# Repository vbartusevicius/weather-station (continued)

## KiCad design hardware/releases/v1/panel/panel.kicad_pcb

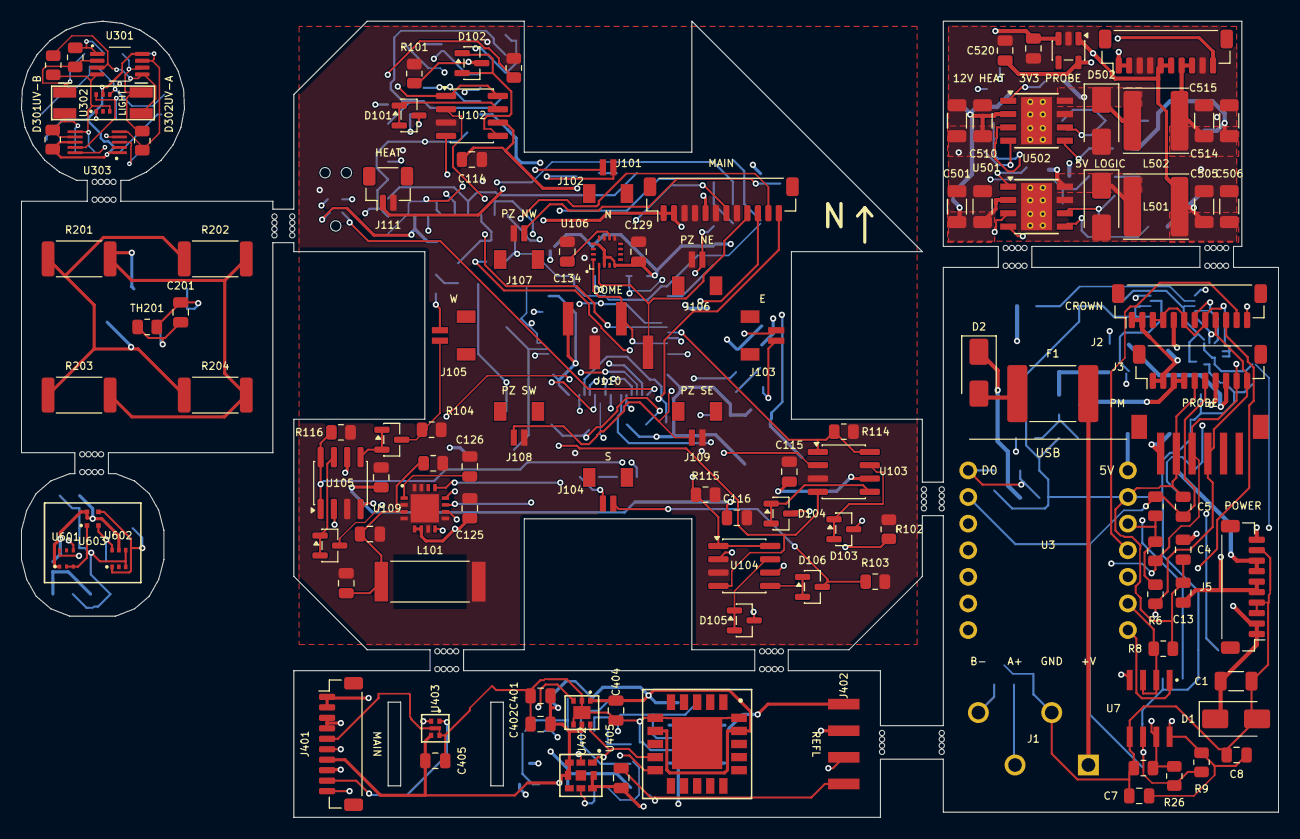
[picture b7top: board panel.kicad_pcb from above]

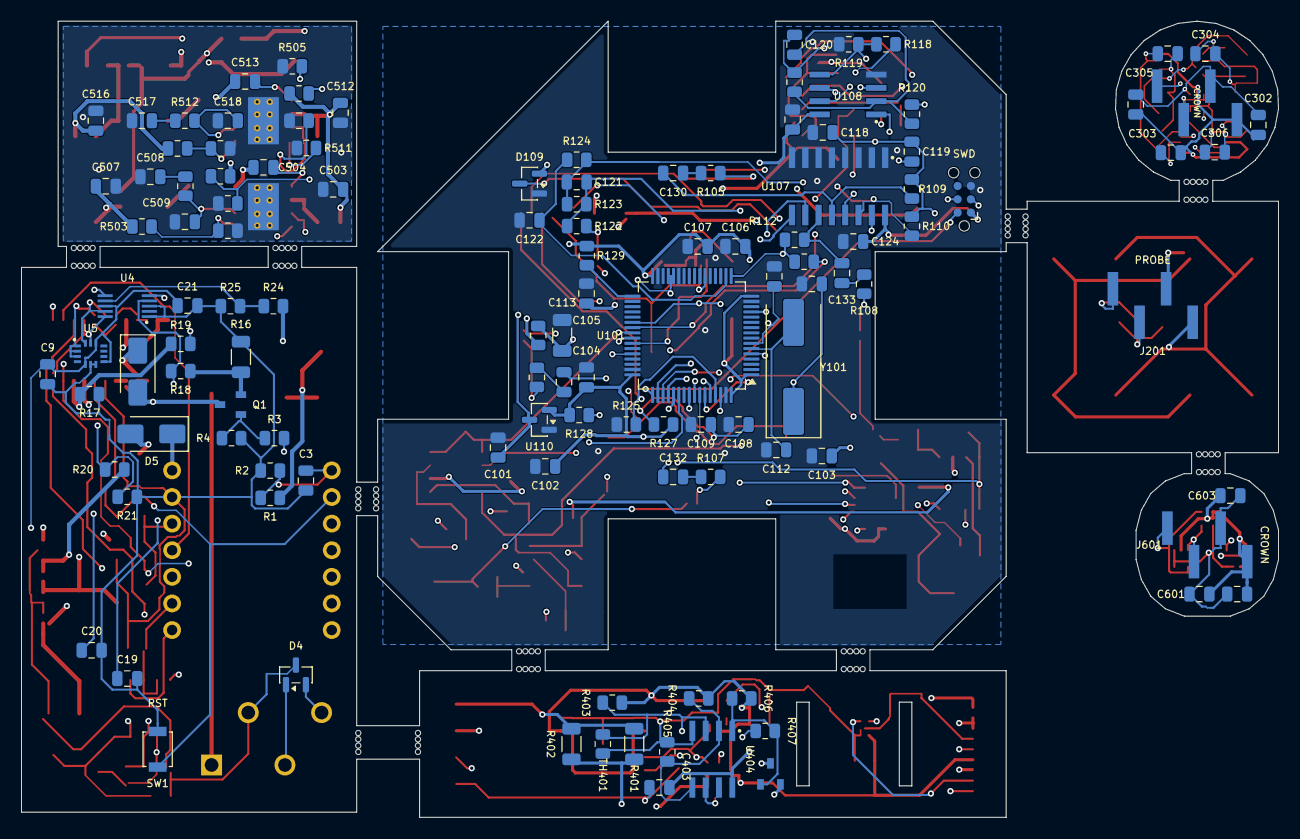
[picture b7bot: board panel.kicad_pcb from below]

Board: 4 copper layers, 120.0 x 76.0 mm, 236 parts (120 on the bottom side), 144 nets.

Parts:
C1, C501, C502, C510, C511: 2u2 100V; C_1206_3216Metric
C3, C5, C7, C8, C9, C21, C103, C104, C105, C106, C109, C110, C119, C123, C124, C129, C201, C301, C302, C303, C402, C403, C404, C405, C406, C504, C507, C513, C516, C601, C602: 100n 50V; C_0805_2012Metric
C4, C13, C102, C107, C134, C401, C520: 10u 10V; C_0805_2012Metric
C19, C20, C101, C108, C114, C115, C116, C117, C118, C125, C126, C306, C519, C603: 1u 50V; C_0805_2012Metric
C111, C112: 33p C0G 50V; C_0805_2012Metric
C113, C514, C515: 22u 25V; C_1206_3216Metric
C120: 220p C0G 50V; C_0805_2012Metric
C121, C305: 22n 50V; C_0805_2012Metric
C122: 1n 50V; C_0805_2012Metric
C127, C128: 470p C0G 50V; C_0805_2012Metric
C130, C131, C132, C133, C304: 10n 50V; C_0805_2012Metric
C503, C512: 100n 100V; C_0805_2012Metric
C505, C506: 47u 10V; C_1206_3216Metric
C508: 33n 50V; C_0805_2012Metric
C509, C518: 68p C0G 50V; C_0805_2012Metric
C517: 18n 50V; C_0805_2012Metric
D1: SMAJ36A; D_SMA
D2, D3: SS16; D_SMA
D4: PSM712; SOT-23
D5: SS14; D_SMA
D101, D102, D103, D104, D105, D106, D107, D108, D109: BAV99; SOT-23
D301: GUVB-C21SD; Genicom_COB2418
D302: GUVA-C22SD; Genicom_COB2418
D501, D502: B360A; D_SMA
F1: 1.1A; Fuse_2920_7451Metric
J1: 12-32V + RS485; TerminalBlock_Kefa_KF250-3.5-4P
J2: Crown board; JST_SH_BM12B-SRSS-TB_1x12-1MP_P1.00mm_Vertical
J3: Probe board; JST_SH_BM10B-SRSS-TB_1x10-1MP_P1.00mm_Vertical
J4: PMSA003I PM; JST_B6B-ZR-SM4-TF
J5: Power board; JST_SH_BM10B-SRSS-TB_1x10-1MP_P1.00mm_Vertical
J101: Main board; JST_SH_BM12B-SRSS-TB_1x12-1MP_P1.00mm_Vertical
J102: XD_N; JST_BM02B-SRSS-TB
J103: XD_E; JST_BM02B-SRSS-TB
J104: XD_S; JST_BM02B-SRSS-TB
J105: XD_W; JST_BM02B-SRSS-TB
J106: PIEZO_NE; JST_BM02B-SRSS-TB
J107: PIEZO_NW; JST_BM02B-SRSS-TB
J108: PIEZO_SW; JST_BM02B-SRSS-TB
J109: PIEZO_SE; JST_BM02B-SRSS-TB
J110: DOME_SOCKET; HX_PZ2.54-1x4P-SMD
J111: AUX 12V_HEAT; JST_SH_BM02B-SRSS-TB_1x02-1MP_P1.00mm_Vertical
J112: SWD; Tag-Connect_TC2030-IDC-NL_2x03_P1.27mm_Vertical
J201: Probe T-Header SMD; HX_PZ2.54-1x4P-SMD
J301, J601: CROWN_RISER; HX_PZ2.54-1x4P-SMD
J401, J501: Main board; JST_SH_BM10B-SRSS-TB_1x10-1MP_P1.00mm_Vertical
J402: Reflector T-Socket SMD; HX_PM2.54-1x4P-RA-SMD
L101: 100uH; AS3935_Antenna_MA5532_SDTR1103
L501: 8.2uH; L_Sunlord_SWPA6045S
L502: 22uH; L_Sunlord_SWPA6045S
MOUSE_BITES: DNP
Q1, Q401: AO3400A; AOS_AO3400A_SOT-23
R1, R4, R303: 100k; R_0805_2012Metric
R2, R7, R8, R21, R24, R25, R118, R119, R125, R126, R128, R129, R304, R403, R404, R406, R510: 10k; R_0805_2012Metric
R3, R101, R102, R103, R104: 330R; R_0805_2012Metric
R5, R6, R113, R114, R115, R116: 2k2; R_0805_2012Metric
R9, R10: 390R; R_0805_2012Metric
R16: 0R1; R_1206_3216Metric
R17: 1R; R_0805_2012Metric
R18, R19, R120, R122: 1k; R_0805_2012Metric
R20: 30k; R_0805_2012Metric
R26: 120R; R_0805_2012Metric
R105, R106, R107, R108, R405: 47k; R_0805_2012Metric
R109, R110, R111, R112: 1M; R_0805_2012Metric
R117, R127: 10R; R_0805_2012Metric
R121: 6k8; R_0805_2012Metric
R123, R302: 4M7; R_0805_2012Metric
R124: 22k; R_0805_2012Metric
R201, R202, R203, R204: 120R; R_2512_6332Metric
R301: 10M; R_0805_2012Metric
R401, R402: 680R; R_1206_3216Metric
R407: 470k; R_0805_2012Metric
R501, R507: 511k; R_0805_2012Metric
R502, R508: 82k5; R_0805_2012Metric
R503: 53k6; R_0805_2012Metric
R504: 10k2; R_0805_2012Metric
R505, R511: 130k; R_0805_2012Metric
R506, R512: 6k49; R_0805_2012Metric
R509: 140k; R_0805_2012Metric
SW1: SERVICE; SW_SPST_B3U-1000P
TH201, TH401: 10k NTC; R_0805_2012Metric
U3: XIAO ESP32C6; XIAO_ESP32C6_Header
U4, U303: ADS1115IDGSR; TI_ADS1115_VSSOP-10
U5: LSM6DS3TR-C; ST_LSM6DS3TR-C_LGA-14
U7: SP3485EN-L/TR; ON_LM393DR2G_SOIC-8
U101: STM32G431RBT6; LQFP-64_10x10mm_P0.5mm
U102, U103, U104, U105: UCC27524ADR; SOIC-8_3.9x4.9mm_P1.27mm
U106: MMC5983MA; MEMSIC_MMC5983MA_LGA-16
U107: 74HC4052D; TI_CD4052BM96_SOIC-16
U108: TLV9062IDR; TI_TLV9062IDR_SOIC-8
U109: AS3935-BQFT; ScioSense_AS3935_QFN-16
U110: XC6206P332MR; SOT-23
U301: TLV9062IDGKR; TI_TLV9062_VSSOP-8
U302, U602: TSL25911FN; AMS_TSL25911FN
U401: SCD41-D-R2; Sensirion_SCD41_LGA-20
U402: SGP41-D-R4; Sensirion_SGP41_DFN-6
U403: SHT40-AD1F-R2; Sensirion_SHT45_DFN-4
U404: LM2903DR2G; ON_LM393DR2G_SOIC-8
U405: BMP585; Bosch_BMP585_LGA-9
U501, U502: TPS54360DDAR; TI_SO-PowerPAD-8_ThermalVias
U503: AP2112K-3.3; SOT-23-5
U601: LTR-390UV-01; LiteOn_LTR-390UV-01
U603: GUVB-C31SM; GenUV_GUVB-C31SM
Y101: 8MHz; Crystal_SMD_HC49-SD

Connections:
+3V3: C7.1, C8.1, C9.1, C21.1, R5.1, R6.1, R7.1, R9.1, U3.12, U4.8, U5.5, U5.8, U5.12, U7.8
+3V3_PROBE: J3.7, J5.10
+5V: C13.1, D5.2, J2.5, J4.1, J5.5, J5.6, R24.1
+5V_XIAO: C4.1, D5.1, U3.14
+12V_HEAT: D3.1, J2.1, J2.2, J3.1, J3.2, J5.7, J5.8, R20.1
CO2_HEAT_RTN: J3.8, R17.1, R19.1
CROWN_+3V3: C102.1, C103.1, C104.1, C105.1, C106.1, C107.1, C123.1, C124.1, C125.1, C129.1, D109.2, J110.1, J112.1, R127.1, R128.2, R129.2, U101.1, U101.16, U101.32, U101.48, U101.64, U106.2, U106.4, U106.13, U107.16, U108.8, U109.5, U109.6, U110.2
CROWN_+3V3A: C108.1, C109.1, R118.1, R127.2, U101.28, U101.29
CROWN_+5V: C101.1, J101.5, U110.3
CROWN_+12V_HEAT: J101.1, J101.2, J111.1, R117.1
CROWN_AS_ACG: C126.1, U109.1
CROWN_AS_CS: U101.51, U109.8
CROWN_AS_INP: C127.1, C128.1, L101.1, R126.1, U109.3
CROWN_AS_IRQ: U101.62, U109.10
CROWN_AS_MISO: U101.57, U109.12
CROWN_AS_MOSI: U101.58, U109.13
CROWN_AS_SCK: U101.56, U109.11
CROWN_BL_PA10: R128.1, U101.44
CROWN_BL_PB12: R129.1, U101.33
CROWN_BOOT0: J2.12, U3.3
CROWN_CROWN_BOOT0: J101.12, R125.1, U101.61
CROWN_CROWN_IRQ: J101.10, U101.54
CROWN_CROWN_NRST: C110.1, J101.11, J112.3, U101.7
CROWN_GND: C101.2, C102.2, C103.2, C104.2, C105.2, C106.2, C107.2, C108.2, C109.2, C110.2, C111.2, C112.2, C113.2, C114.2, C115.2, C116.2, C117.2, C118.2, C122.2, C123.2, C124.2, C125.2, C126.2, C127.2, C128.2, C129.2, C134.2, D109.1, J101.3, J101.4, J101.6, J101.8, J106.2, J107.2, J108.2, J109.2, J110.2, J111.2, J112.5, L101.2, R101.2, R102.2, R103.2, R104.2, R113.2, R114.2, R115.2, R116.2, R119.2, R125.2, R126.2, U101.15, U101.27, U101.31, U101.47, U101.63, U102.3, U103.3, U104.3, U105.3, U106.9, U106.11, U107.1, U107.2, U107.3, U107.4, U107.5, U107.6, U107.7, U107.8, U108.4, U109.2, U109.4, U109.7, U109.9, U109.15, U109.16, U109.17, U110.1
CROWN_I2C_SCL: J101.9, J110.4, U101.22, U106.1
CROWN_I2C_SDA: J101.7, J110.3, U101.42, U106.16
CROWN_IRQ: J2.10, U3.10
CROWN_MAG_CAP: C134.1, U106.10
CROWN_MUX_S0: U101.59, U107.10
CROWN_MUX_S1: U101.60, U107.9
CROWN_NRST: J2.11, U3.11
CROWN_PIEZO_IN: D109.3, J106.1, J107.1, J108.1, J109.1, R122.1
CROWN_PIEZO_INV: C121.1, R122.2, R123.1, U108.6
CROWN_PIEZO_OUT: C121.2, R123.2, R124.1, U108.7
CROWN_RAIN_ADC: C122.1, R124.2, U101.18
CROWN_SWCLK: J112.4, U101.50
CROWN_SWDIO: J112.2, U101.49
CROWN_TX_N: U101.52, U102.4, U103.4, U104.4, U105.4
CROWN_TX_P: U101.38, U102.2, U103.2, U104.2, U105.2
CROWN_US_AMP_FB: C120.1, R120.1, R121.1, U108.2
CROWN_US_AMP_G: C119.1, R120.2
CROWN_US_AMP_OUT: C120.2, R121.2, U101.13, U108.1
CROWN_US_RX_MUX: U107.13, U108.3
CROWN_US_VREF: C118.1, C119.2, R109.2, R110.2, R111.2, R112.2, R118.2, R119.1, U101.17, U108.5
CROWN_VDRV: C113.1, C114.1, C115.1, C116.1, C117.1, R117.2, U102.6, U103.6, U104.6, U105.6
CROWN_XD_EN_E: R114.1, U101.40, U103.1, U103.8
CROWN_XD_EN_N: R113.1, U101.39, U102.1, U102.8
CROWN_XD_EN_S: R115.1, U101.41, U104.1, U104.8
CROWN_XD_EN_W: R116.1, U101.53, U105.1, U105.8
CROWN_XD_E_A: D103.3, J103.1, R106.1
CROWN_XD_E_B: D104.3, J103.2, R102.1
CROWN_XD_E_OUT_A: D103.1, D103.2, U103.7
CROWN_XD_E_OUT_B: D104.1, D104.2, U103.5
CROWN_XD_E_RX: C131.2, R110.1, U107.14
CROWN_XD_E_RXC: C131.1, R106.2
CROWN_XD_N_A: D101.3, J102.1, R105.1
CROWN_XD_N_B: D102.3, J102.2, R101.1
CROWN_XD_N_OUT_A: D101.1, D101.2, U102.7
CROWN_XD_N_OUT_B: D102.1, D102.2, U102.5
CROWN_XD_N_RX: C130.2, R109.1, U107.12
CROWN_XD_N_RXC: C130.1, R105.2
CROWN_XD_S_A: D105.3, J104.1, R107.1
CROWN_XD_S_B: D106.3, J104.2, R103.1
CROWN_XD_S_OUT_A: D105.1, D105.2, U104.7
CROWN_XD_S_OUT_B: D106.1, D106.2, U104.5
CROWN_XD_S_RX: C132.2, R111.1, U107.15
CROWN_XD_S_RXC: C132.1, R107.2
CROWN_XD_W_A: D107.3, J105.1, R108.1
CROWN_XD_W_B: D108.3, J105.2, R104.1
CROWN_XD_W_OUT_A: D107.1, D107.2, U105.7
CROWN_XD_W_OUT_B: D108.1, D108.2, U105.5
CROWN_XD_W_RX: C133.2, R112.1, U107.11
CROWN_XD_W_RXC: C133.1, R108.2
CROWN_XTAL_IN: C111.1, U101.5, Y101.1
CROWN_XTAL_OUT: C112.1, U101.6, Y101.2
DOME_+3V3: C301.1, C302.1, C303.1, J301.1, R303.1, U301.8, U302.5, U303.1, U303.8
DOME_GND: C301.2, C302.2, C303.2, C306.2, J301.2, R304.2, U301.4, U302.3, U302.4, U303.3, U303.6
DOME_I2C_SCL: J301.4, U302.1, U303.10
DOME_I2C_SDA: J301.3, U302.6, U303.9
DOME_LEGACY_+3V3: C601.1, C602.1, C603.1, J601.1, U601.1, U602.5, U603.4
DOME_LEGACY_GND: C601.2, C602.2, C603.2, J601.2, U601.2, U601.3, U602.3, U602.4, U603.1
DOME_LEGACY_I2C_SCL: J601.4, U601.4, U602.1, U603.3
DOME_LEGACY_I2C_SDA: J601.3, U601.6, U602.6, U603.2
DOME_UVA_IN: C305.1, D302.2, R302.1, U301.6
DOME_UVA_OUT: C305.2, R302.2, U301.7, U303.5
DOME_UVB_IN: C304.1, D301.2, R301.1, U301.2
DOME_UVB_OUT: C304.2, R301.2, U301.1, U303.4
DOME_UV_VB: C306.1, D301.1, D302.1, R303.2, R304.1, U301.3, U301.5, U303.7
GND: C1.2, C3.2, C4.2, C5.2, C7.2, C8.2, C9.2, C13.2, C19.2, C20.2, C21.2, D1.2, D4.3, J1.2, J2.3, J2.4, J2.6, J2.8, J3.5, J4.2, J5.3, J5.4, J5.9, R2.2, R4.2, R8.2, R10.2, R16.2, R17.2, R21.2, R25.2, SW1.2, U3.13, U4.1, U4.3, U5.1, U5.2, U5.3, U5.6, U5.7, U7.5
HEAT_GATE: Q1.1, R3.2, R4.1
HEAT_PWM: R3.1, U3.4
HEAT_SENSE: Q1.2, R16.1, R18.1
HEAT_SW: D3.2, J3.3, J3.4, Q1.3
I2C_SCL: J2.9, J3.10, J4.4, R6.2, U3.6, U4.10, U5.13
I2C_SDA: J2.7, J3.9, J4.3, R5.2, U3.5, U4.9, U5.14
MON_5V: R20.2, R21.1, U4.6
MON_5V_LOGIC: R24.2, R25.1, U4.7
MON_PROBE: C20.1, R19.2, U4.5
MON_REFL: C19.1, R18.2, U4.4
NTC_SENSE: C5.1, J3.6, R7.2, SW1.1, U3.2
POWER_+3V3_PROBE: C520.1, J501.10, U503.5
POWER_+5V: C505.1, C506.1, C507.1, C519.1, J501.5, J501.6, L501.2, R503.1, U503.1, U503.3
POWER_+12V_HEAT: C514.1, C515.1, C516.1, J501.7, J501.8, L502.2, R509.1
POWER_GND: C501.2, C502.2, C503.2, C505.2, C506.2, C507.2, C508.2, C509.2, C510.2, C511.2, C512.2, C514.2, C515.2, C516.2, C517.2, C518.2, C519.2, C520.2, D501.2, D502.2, J501.3, J501.4, J501.9, R502.2, R504.2, R505.2, R508.2, R510.2, R511.2, U501.7, U501.9, U502.7, U502.9, U503.2
POWER_HEAT_BST: C513.1, U502.1
POWER_HEAT_CC: C517.1, R512.2
POWER_HEAT_COMP: C518.1, R512.1, U502.6
POWER_HEAT_EN: R507.2, R508.1, U502.3
POWER_HEAT_FB: R509.2, R510.1, U502.5
POWER_HEAT_RT: R511.1, U502.4
POWER_HEAT_SW: C513.2, D502.1, L502.1, U502.8
POWER_LOGIC_BST: C504.1, U501.1
POWER_LOGIC_CC: C508.1, R506.2
POWER_LOGIC_COMP: C509.1, R506.1, U501.6
POWER_LOGIC_EN: R501.2, R502.1, U501.3
POWER_LOGIC_FB: R503.2, R504.1, U501.5
POWER_LOGIC_RT: R505.1, U501.4
POWER_LOGIC_SW: C504.2, D501.1, L501.1, U501.8
POWER_VIN_PROT: C501.1, C502.1, C503.1, C510.1, C511.1, C512.1, J501.1, J501.2, R501.1, R507.1, U501.2, U502.2
PROBE_+3V3_PROBE: C401.1, C402.1, C404.1, C405.1, C406.1, J401.7, R403.1, R404.1, R406.1, U401.7, U401.19, U402.1, U402.5, U403.3, U405.3, U405.4, U405.7, U405.8
PROBE_+12V_HEAT: C403.1, J401.1, J401.2, J402.1, R401.1, R402.1, U404.8
PROBE_CO2_GATE: Q401.1, R406.2, R407.1, U404.1
PROBE_CO2_HEAT_RTN: J401.8, Q401.2
PROBE_CO2_HEAT_SW: Q401.3, R401.2, R402.2
PROBE_CO2_NTC: R403.2, R407.2, TH401.1, U404.3
PROBE_CO2_VSET: R404.2, R405.1, U404.2, U404.5
PROBE_GND: C401.2, C402.2, C403.2, C404.2, C405.2, C406.2, J401.5, J402.4, R405.2, TH401.2, U401.6, U401.20, U401.21, U402.2, U402.4, U402.7, U403.4, U403.5, U404.4, U404.6, U405.6
PROBE_HEAT_SW: J401.3, J401.4, J402.2
PROBE_I2C_SCL: J401.10, U401.9, U402.6, U403.2, U405.1
PROBE_I2C_SDA: J401.9, U401.10, U402.3, U403.1, U405.2
PROBE_NTC_SENSE: J401.6, J402.3
REFLECTOR_+12V_HEAT: J201.1, R201.1, R202.1, R203.1, R204.1
REFLECTOR_GND: C201.2, J201.4, TH201.2
REFLECTOR_HEAT_SW: J201.2, R201.2, R202.2, R203.2, R204.2
REFLECTOR_NTC_SENSE: C201.1, J201.3, TH201.1
RS485_A: D4.1, J1.3, R9.2, R26.1, U7.6
RS485_B: D4.2, J1.4, R10.1, R26.2, U7.7
RS485_DE: R8.1, U3.9, U7.2, U7.3
RS485_RX: U3.8, U7.1
RS485_TX: U3.7, U7.4
VIN_ADC: C3.1, R1.2, R2.1, U3.1
VIN_FUSED: D2.2, F1.2
VIN_PROT: C1.1, D1.1, D2.1, J5.1, J5.2, R1.1
VIN_RAW: F1.1, J1.1

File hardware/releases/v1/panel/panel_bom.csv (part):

Line,Qty,Designators,Value,Package,Type,Manufacturer,MPN,LCSC,Assembly
1,5,"C1,C501,C502,C510,C511",2u2 100V,C_1206_3216Metric,SMD,Samsung,CL31B225KCHSNNE,C170101,machine
2,14,"C101,C108,C114,C115,C116,C117,C118,C125,C126,C19,C20,C306,C519,C603",1u 50V,C_0805_2012Metric,SMD,Samsung,CL21B105KBFNNNE,C28323,machine
3,7,"C102,C107,C13,C134,C4,C401,C520",10u 10V,C_0805_2012Metric,SMD,Samsung,CL21A106KPFNNNE,C17024,machine
4,31,"C103,C104,C105,C106,C109,C110,C119,C123,C124,C129,C201,C21,C3,C301,C302,C303,C402,C403,C404,C405,C406,C5,C504,C507,C513,C516,C601,C602,C7,C8,C9",100n 50V,C_0805_2012Metric,SMD,YAGEO,CC0805KRX7R9BB104,C49678,machine
5,2,"C111,C112",33p C0G 50V,C_0805_2012Metric,SMD,YAGEO,CC0805JRNPO9BN330,C107115,machine
6,3,"C113,C514,C515",22u 25V,C_1206_3216Metric,SMD,Samsung,CL31A226KAHNNNE,C12891,machine
7,1,C120,220p C0G 50V,C_0805_2012Metric,SMD,YAGEO,CC0805JRNPO9BN221,C107112,machine
8,2,"C121,C305",22n 50V,C_0805_2012Metric,SMD,YAGEO,CC0805KRX7R9BB223,C107147,machine
9,1,C122,1n 50V,C_0805_2012Metric,SMD,YAGEO,CC0805KRX7R9BB102,C94121,machine
10,2,"C127,C128",470p C0G 50V,C_0805_2012Metric,SMD,YAGEO,CC0805JRNPO9BN471,C62771,machine
11,5,"C130,C131,C132,C133,C304",10n 50V,C_0805_2012Metric,SMD,YAGEO,CC0805KRX7R9BB103,C83170,machine
12,2,"C503,C512",100n 100V,C_0805_2012Metric,SMD,YAGEO,CC0805KKX7R0BB104,C106243,machine
13,2,"C505,C506",47u 10V,C_1206_3216Metric,SMD,Samsung,CL31A476MPHNNNE,C96123,machine
14,1,C508,33n 50V,C_0805_2012Metric,SMD,YAGEO,CC0805KRX7R9BB333,C107150,machine
15,2,"C509,C518",68p C0G 50V,C_0805_2012Metric,SMD,YAGEO,CC0805JRNPO9BN680,C107120,machine
16,1,C517,18n 50V,C_0805_2012Metric,SMD,YAGEO,CC0805JRX7R9BB183,C520032,machine
17,1,D1,SMAJ36A,D_SMA,SMD,MDD,SMAJ36A,C113967,machine
18,9,"D101,D102,D103,D104,D105,D106,D107,D108,D109",BAV99,SOT-23,SMD,Nexperia,"BAV99,215",C2500,machine
19,2,"D2,D3",SS16,D_SMA,SMD,MDD,SS16,C2481,machine
20,1,D301,GUVB-C21SD,Genicom_COB2418,SMD,Genicom,GUVB-C21SD,,hand-fit (not stocked by JLCPCB)
21,1,D302,GUVA-C22SD,Genicom_COB2418,SMD,Genicom,GUVA-C22SD,,hand-fit (not stocked by JLCPCB)
22,1,D4,PSM712,SOT-23,SMD,Protek,PSM712-LF-T7,C32677,machine
23,1,D5,SS14,D_SMA,SMD,MDD,SS14,C2480,machine
24,2,"D501,D502",B360A,D_SMA,SMD,Diodes Inc,B360A-13-F,C94193,machine
25,1,F1,1.1A,Fuse_2920_7451Metric,SMD,Littelfuse,2920L110/60V,C49318488,machine
26,1,J1,12-32V + RS485,TerminalBlock_Kefa_KF250-3.5-4P,THT,Cixi Kefa Elec,KF250-3.5-4P-1,C475156,machine
27,1,J101,Main board,JST_SH_BM12B-SRSS-TB_1x12-1MP_P1.00mm_Vertical,SMD,JST,BM12B-SRSS-TB(LF)(SN),C160398,machine
28,1,J102,XD_N,JST_BM02B-SRSS-TB,SMD,JST,BM02B-SRSS-TB(LF)(SN),C160388,machine
29,1,J103,XD_E,JST_BM02B-SRSS-TB,SMD,JST,BM02B-SRSS-TB(LF)(SN),C160388,machine
30,1,J104,XD_S,JST_BM02B-SRSS-TB,SMD,JST,BM02B-SRSS-TB(LF)(SN),C160388,machine
31,1,J105,XD_W,JST_BM02B-SRSS-TB,SMD,JST,BM02B-SRSS-TB(LF)(SN),C160388,machine
32,1,J106,PIEZO_NE,JST_BM02B-SRSS-TB,SMD,JST,BM02B-SRSS-TB(LF)(SN),C160388,machine
33,1,J107,PIEZO_NW,JST_BM02B-SRSS-TB,SMD,JST,BM02B-SRSS-TB(LF)(SN),C160388,machine
34,1,J108,PIEZO_SW,JST_BM02B-SRSS-TB,SMD,JST,BM02B-SRSS-TB(LF)(SN),C160388,machine
35,1,J109,PIEZO_SE,JST_BM02B-SRSS-TB,SMD,JST,BM02B-SRSS-TB(LF)(SN),C160388,machine
36,1,J110,DOME_SOCKET,HX_PZ2.54-1x4P-SMD,SMD,HCTL,HX PM2.54-1x4P TP-YQ,C42379197,machine
37,1,J111,AUX 12V_HEAT,JST_SH_BM02B-SRSS-TB_1x02-1MP_P1.00mm_Vertical,SMD,JST,BM02B-SRSS-TB(LF)(SN),C160388,machine
38,1,J2,Crown board,JST_SH_BM12B-SRSS-TB_1x12-1MP_P1.00mm_Vertical,SMD,JST,BM12B-SRSS-TB(LF)(SN),C160398,machine
39,1,J201,Probe T-Header SMD,HX_PZ2.54-1x4P-SMD,SMD,HANBO,HX PZ2.54-1x4P TP-YQ,C41417361,machine
40,1,J3,Probe board,JST_SH_BM10B-SRSS-TB_1x10-1MP_P1.00mm_Vertical,SMD,JST,BM10B-SRSS-TB(LF)(SN),C160396,machine
41,2,"J301,J601",CROWN_RISER,HX_PZ2.54-1x4P-SMD,SMD,HCTL,HX PZ2.54-1x4P TP-YQ,C41417361,machine
42,1,J4,PMSA003I PM,JST_B6B-ZR-SM4-TF,SMD,JST,B6B-ZR-SM4-TF(LF)(SN),C471473,machine
43,2,"J401,J501",Main board,JST_SH_BM10B-SRSS-TB_1x10-1MP_P1.00mm_Vertical,SMD,JST,BM10B-SRSS-TB(LF)(SN),C160396,machine
44,1,J402,Reflector T-Socket SMD,HX_PM2.54-1x4P-RA-SMD,SMD,HANBO,HX PM2.54-1x4P WT,C46061768,machine
45,1,J5,Power board,JST_SH_BM10B-SRSS-TB_1x10-1MP_P1.00mm_Vertical,SMD,JST,BM10B-SRSS-TB(LF)(SN),C160396,machine
46,1,L101,100uH,AS3935_Antenna_MA5532_SDTR1103,SMD,Coilcraft,MA5532-AE,,hand-fit (not stocked by JLCPCB)
47,1,L501,8.2uH,L_Sunlord_SWPA6045S,SMD,APV,ANR6045T8R2M,C7427168,machine
48,1,L502,22uH,L_Sunlord_SWPA6045S,SMD,Bourns,SRN6045TA-220M,C2044314,machine
49,2,"Q1,Q401",AO3400A,AOS_AO3400A_SOT-23,SMD,Alpha & Omega Semicon,AO3400A,C20917,machine
50,3,"R1,R303,R4",100k,R_0805_2012Metric,SMD,UNI-ROYAL,0805W8F1003T5E,C149504,machine
51,2,"R10,R9",390R,R_0805_2012Metric,SMD,UNI-ROYAL,0805W8F3900T5E,C17655,machine
52,5,"R101,R102,R103,R104,R3",330R,R_0805_2012Metric,SMD,UNI-ROYAL,0805W8F3300T5E,C17630,machine
53,5,"R105,R106,R107,R108,R405",47k,R_0805_2012Metric,SMD,UNI-ROYAL,0805W8F4702T5E,C17713,machine
54,4,"R109,R110,R111,R112",1M,R_0805_2012Metric,SMD,UNI-ROYAL,0805W8F1004T5E,C17514,machine
55,6,"R113,R114,R115,R116,R5,R6",2k2,R_0805_2012Metric,SMD,UNI-ROYAL,0805W8F2201T5E,C17520,machine
56,2,"R117,R127",10R,R_0805_2012Metric,SMD,UNI-ROYAL,0805W8F100JT5E,C17415,machine
57,17,"R118,R119,R125,R126,R128,R129,R2,R21,R24,R25,R304,R403,R404,R406,R510,R7,R8",10k,R_0805_2012Metric,SMD,UNI-ROYAL,0805W8F1002T5E,C17414,machine
58,4,"R120,R122,R18,R19",1k,R_0805_2012Metric,SMD,UNI-ROYAL,0805W8F1001T5E,C17513,machine
59,1,R121,6k8,R_0805_2012Metric,SMD,UNI-ROYAL,0805W8F6801T5E,C17772,machine
60,2,"R123,R302",4M7,R_0805_2012Metric,SMD,UNI-ROYAL,0805W8F4704T5E,C17674,machine
61,1,R124,22k,R_0805_2012Metric,SMD,UNI-ROYAL,0805W8F2202T5E,C17560,machine
62,1,R16,0R1,R_1206_3216Metric,SMD,UNI-ROYAL,1206W4F100LT5E,C25334,machine
63,1,R17,1R,R_0805_2012Metric,SMD,UNI-ROYAL,0805W8F100KT5E,C25271,machine
64,1,R20,30k,R_0805_2012Metric,SMD,UNI-ROYAL,0805W8F3002T5E,C17621,machine
65,4,"R201,R202,R203,R204",120R,R_2512_6332Metric,SMD,YAGEO,RC2512FK-7W120RL,C7276687,machine
66,1,R26,120R,R_0805_2012Metric,SMD,UNI-ROYAL,0805W8F1200T5E,C17437,hand-fit (not stocked by JLCPCB)
67,1,R301,10M,R_0805_2012Metric,SMD,UNI-ROYAL,0805W8F1005T5E,C26108,machine
68,2,"R401,R402",680R,R_1206_3216Metric,SMD,FOJAN,FRP1206F6800TS,C48533685,machine
69,1,R407,470k,R_0805_2012Metric,SMD,UNI-ROYAL,0805W8F4703T5E,C17709,machine
70,2,"R501,R507",511k,R_0805_2012Metric,SMD,UNI-ROYAL,0805W8F5113T5E,C17735,machine
71,2,"R502,R508",82k5,R_0805_2012Metric,SMD,YAGEO,RC0805FR-0782K5L,C276314,machine
72,1,R503,53k6,R_0805_2012Metric,SMD,UNI-ROYAL,0805W8F5362T5E,C21398,machine
73,1,R504,10k2,R_0805_2012Metric,SMD,UNI-ROYAL,0805W8F1022T5E,C17402,machine
74,2,"R505,R511",130k,R_0805_2012Metric,SMD,UNI-ROYAL,0805W8F1303T5E,C17450,machine
75,2,"R506,R512",6k49,R_0805_2012Metric,SMD,UNI-ROYAL,0805W8F6491T5E,C17769,machine
76,1,R509,140k,R_0805_2012Metric,SMD,UNI-ROYAL,0805W8F1403T5E,C17460,machine
77,1,SW1,SERVICE,SW_SPST_B3U-1000P,SMD,Omron,B3U-1000P,C231329,machine
78,2,"TH201,TH401",10k NTC,R_0805_2012Metric,SMD,R+O,HNTC0805-103F3950FB,C49247662,machine
79,1,U101,STM32G431RBT6,LQFP-64_10x10mm_P0.5mm,SMD,STMicroelectronics,STM32G431RBT6,C431633,machine
80,4,"U102,U103,U104,U105",UCC27524ADR,SOIC-8_3.9x4.9mm_P1.27mm,SMD,Texas Instruments,UCC27524ADR,C185857,machine
81,1,U106,MMC5983MA,MEMSIC_MMC5983MA_LGA-16,SMD,MEMSIC,MMC5983MA,C404329,machine
82,1,U107,74HC4052D,TI_CD4052BM96_SOIC-16,SMD,Nexperia,"74HC4052D,653",C11350,machine
83,1,U108,TLV9062IDR,TI_TLV9062IDR_SOIC-8,SMD,Texas Instruments,TLV9062IDR,C398355,machine
84,1,U109,AS3935-BQFT,ScioSense_AS3935_QFN-16,SMD,ScioSense,AS3935-BQFT,,hand-fit (not stocked by JLCPCB)
85,1,U110,XC6206P332MR,SOT-23,SMD,Torex,XC6206P332MR-G,C5446,machine
86,1,U3,XIAO ESP32C6,XIAO_ESP32C6_Header,THT,Seeed Studio,102010636,,hand-fit (not stocked by JLCPCB)
87,1,U301,TLV9062IDGKR,TI_TLV9062_VSSOP-8,SMD,Texas Instruments,TLV9062IDGKR,C398356,machine
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
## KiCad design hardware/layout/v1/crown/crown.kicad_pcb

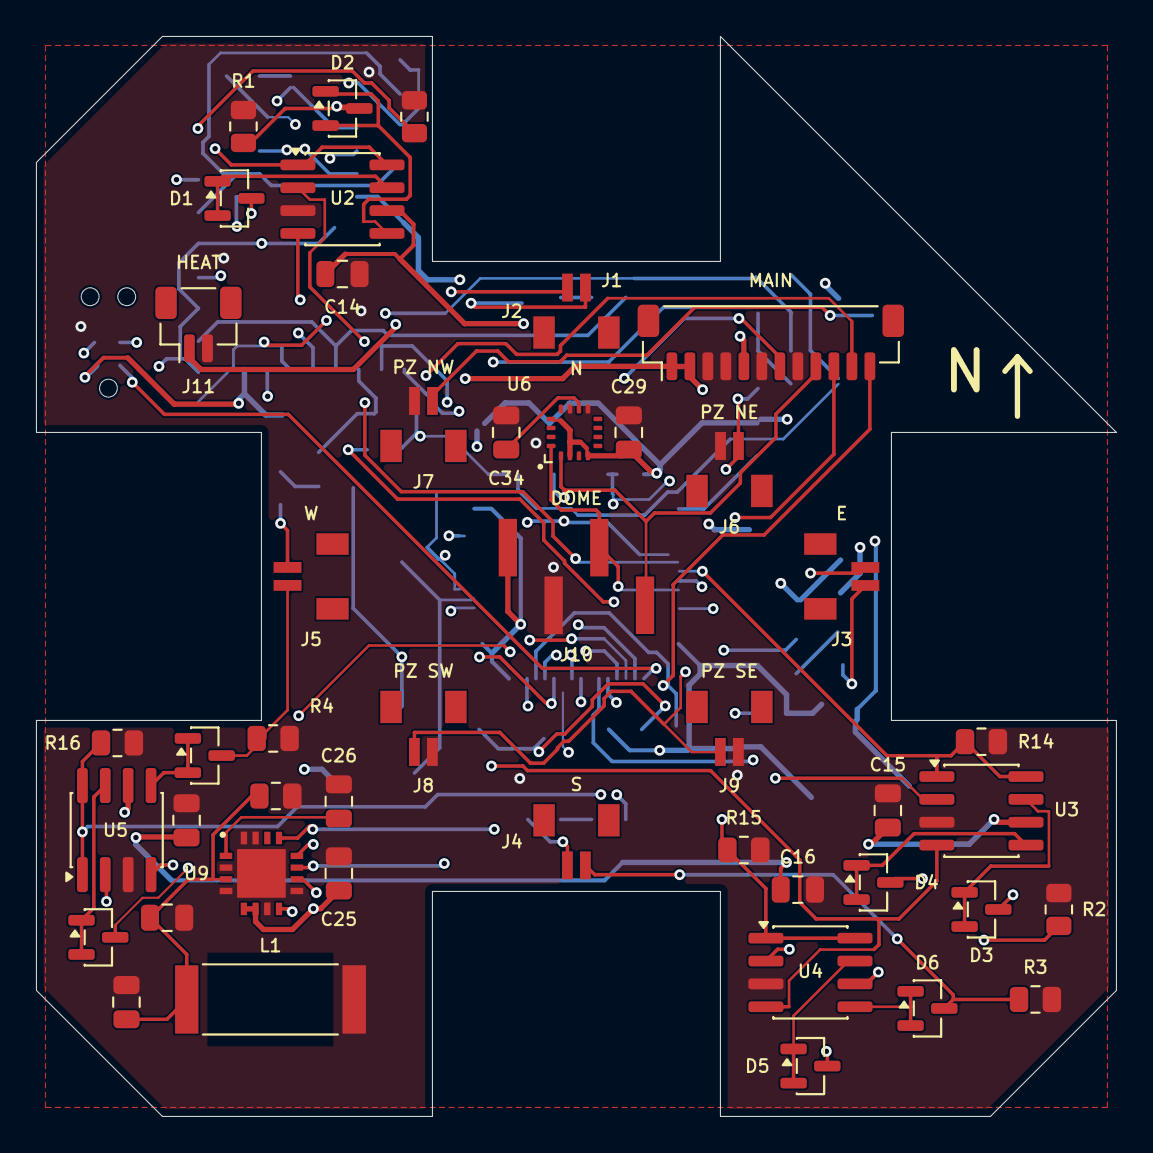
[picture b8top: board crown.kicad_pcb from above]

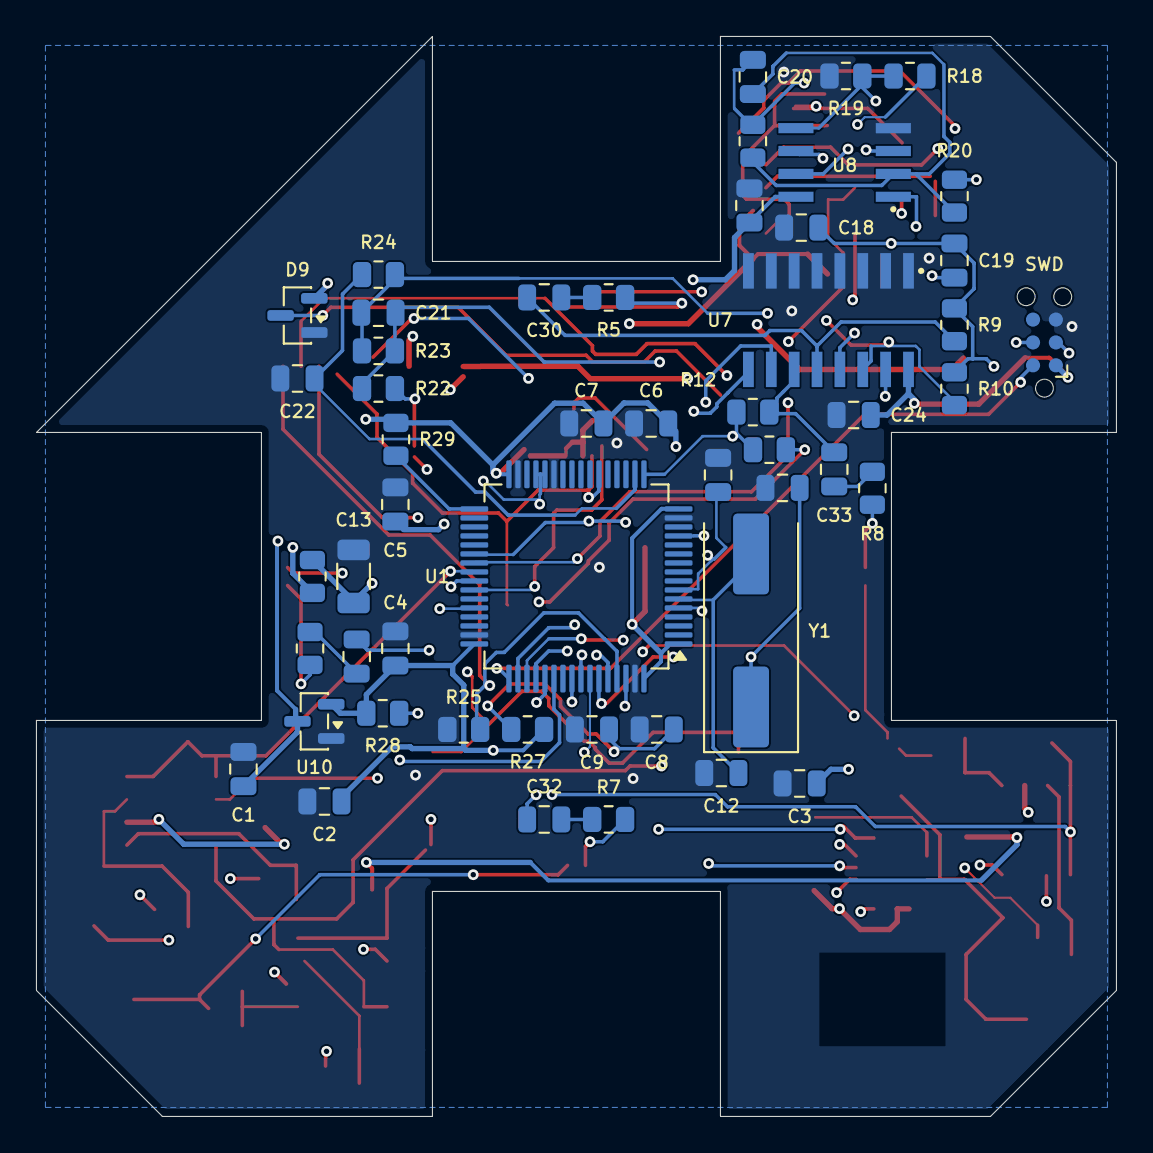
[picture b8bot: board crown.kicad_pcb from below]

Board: 4 copper layers, 60.0 x 60.0 mm, 96 parts (51 on the bottom side), 66 nets.

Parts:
C1, C8, C14, C15, C16, C17, C18, C25, C26: 1u 50V; C_0805_2012Metric
C2, C7, C34: 10u 10V; C_0805_2012Metric
C3, C4, C5, C6, C9, C10, C19, C23, C24, C29: 100n 50V; C_0805_2012Metric
C11, C12: 33p C0G 50V; C_0805_2012Metric
C13: 22u 25V; C_1206_3216Metric
C20: 220p C0G 50V; C_0805_2012Metric
C21: 22n 50V; C_0805_2012Metric
C22: 1n 50V; C_0805_2012Metric
C27, C28: 470p C0G 50V; C_0805_2012Metric
C30, C31, C32, C33: 10n 50V; C_0805_2012Metric
D1, D2, D3, D4, D5, D6, D7, D8, D9: BAV99; SOT-23
J1: Main board; JST_SH_BM12B-SRSS-TB_1x12-1MP_P1.00mm_Vertical
J2: XD_N; JST_BM02B-SRSS-TB
J3: XD_E; JST_BM02B-SRSS-TB
J4: XD_S; JST_BM02B-SRSS-TB
J5: XD_W; JST_BM02B-SRSS-TB
J6: PIEZO_NE; JST_BM02B-SRSS-TB
J7: PIEZO_NW; JST_BM02B-SRSS-TB
J8: PIEZO_SW; JST_BM02B-SRSS-TB
J9: PIEZO_SE; JST_BM02B-SRSS-TB
J10: DOME_SOCKET; HX_PZ2.54-1x4P-SMD
J11: AUX 12V_HEAT; JST_SH_BM02B-SRSS-TB_1x02-1MP_P1.00mm_Vertical
J12: SWD; Tag-Connect_TC2030-IDC-NL_2x03_P1.27mm_Vertical
L1: 100uH; AS3935_Antenna_MA5532_SDTR1103
R1, R2, R3, R4: 330R; R_0805_2012Metric
R5, R6, R7, R8: 47k; R_0805_2012Metric
R9, R10, R11, R12: 1M; R_0805_2012Metric
R13, R14, R15, R16: 2k2; R_0805_2012Metric
R17, R27: 10R; R_0805_2012Metric
R18, R19, R25, R26, R28, R29: 10k; R_0805_2012Metric
R20, R22: 1k; R_0805_2012Metric
R21: 6k8; R_0805_2012Metric
R23: 4M7; R_0805_2012Metric
R24: 22k; R_0805_2012Metric
U1: STM32G431RBT6; LQFP-64_10x10mm_P0.5mm
U2, U3, U4, U5: UCC27524ADR; SOIC-8_3.9x4.9mm_P1.27mm
U6: MMC5983MA; MEMSIC_MMC5983MA_LGA-16
U7: 74HC4052D; TI_CD4052BM96_SOIC-16
U8: TLV9062IDR; TI_TLV9062IDR_SOIC-8
U9: AS3935-BQFT; ScioSense_AS3935_QFN-16
U10: XC6206P332MR; SOT-23
Y1: 8MHz; Crystal_SMD_HC49-SD

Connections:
+3V3: C2.1, C3.1, C4.1, C5.1, C6.1, C7.1, C23.1, C24.1, C25.1, C29.1, D9.2, J10.1, J12.1, R27.1, R28.2, R29.2, U1.1, U1.16, U1.32, U1.48, U1.64, U6.2, U6.4, U6.13, U7.16, U8.8, U9.5, U9.6, U10.2
+3V3A: C8.1, C9.1, R18.1, R27.2, U1.28, U1.29
+5V: C1.1, J1.5, U10.3
+12V_HEAT: J1.1, J1.2, J11.1, R17.1
AS_ACG: C26.1, U9.1
AS_CS: U1.51, U9.8
AS_INP: C27.1, C28.1, L1.1, R26.1, U9.3
AS_IRQ: U1.62, U9.10
AS_MISO: U1.57, U9.12
AS_MOSI: U1.58, U9.13
AS_SCK: U1.56, U9.11
BL_PA10: R28.1, U1.44
BL_PB12: R29.1, U1.33
CROWN_BOOT0: J1.12, R25.1, U1.61
CROWN_IRQ: J1.10, U1.54
CROWN_NRST: C10.1, J1.11, J12.3, U1.7
GND: C1.2, C2.2, C3.2, C4.2, C5.2, C6.2, C7.2, C8.2, C9.2, C10.2, C11.2, C12.2, C13.2, C14.2, C15.2, C16.2, C17.2, C18.2, C22.2, C23.2, C24.2, C25.2, C26.2, C27.2, C28.2, C29.2, C34.2, D9.1, J1.3, J1.4, J1.6, J1.8, J6.2, J7.2, J8.2, J9.2, J10.2, J11.2, J12.5, L1.2, R1.2, R2.2, R3.2, R4.2, R13.2, R14.2, R15.2, R16.2, R19.2, R25.2, R26.2, U1.15, U1.27, U1.31, U1.47, U1.63, U2.3, U3.3, U4.3, U5.3, U6.9, U6.11, U7.1, U7.2, U7.3, U7.4, U7.5, U7.6, U7.7, U7.8, U8.4, U9.2, U9.4, U9.7, U9.9, U9.15, U9.16, U9.17, U10.1
I2C_SCL: J1.9, J10.4, U1.22, U6.1
I2C_SDA: J1.7, J10.3, U1.42, U6.16
MAG_CAP: C34.1, U6.10
MUX_S0: U1.59, U7.10
MUX_S1: U1.60, U7.9
PIEZO_IN: D9.3, J6.1, J7.1, J8.1, J9.1, R22.1
PIEZO_INV: C21.1, R22.2, R23.1, U8.6
PIEZO_OUT: C21.2, R23.2, R24.1, U8.7
RAIN_ADC: C22.1, R24.2, U1.18
SWCLK: J12.4, U1.50
SWDIO: J12.2, U1.49
TX_N: U1.52, U2.4, U3.4, U4.4, U5.4
TX_P: U1.38, U2.2, U3.2, U4.2, U5.2
US_AMP_FB: C20.1, R20.1, R21.1, U8.2
US_AMP_G: C19.1, R20.2
US_AMP_OUT: C20.2, R21.2, U1.13, U8.1
US_RX_MUX: U7.13, U8.3
US_VREF: C18.1, C19.2, R9.2, R10.2, R11.2, R12.2, R18.2, R19.1, U1.17, U8.5
VDRV: C13.1, C14.1, C15.1, C16.1, C17.1, R17.2, U2.6, U3.6, U4.6, U5.6
XD_EN_E: R14.1, U1.40, U3.1, U3.8
XD_EN_N: R13.1, U1.39, U2.1, U2.8
XD_EN_S: R15.1, U1.41, U4.1, U4.8
XD_EN_W: R16.1, U1.53, U5.1, U5.8
XD_E_A: D3.3, J3.1, R6.1
XD_E_B: D4.3, J3.2, R2.1
XD_E_OUT_A: D3.1, D3.2, U3.7
XD_E_OUT_B: D4.1, D4.2, U3.5
XD_E_RX: C31.2, R10.1, U7.14
XD_E_RXC: C31.1, R6.2
XD_N_A: D1.3, J2.1, R5.1
XD_N_B: D2.3, J2.2, R1.1
XD_N_OUT_A: D1.1, D1.2, U2.7
XD_N_OUT_B: D2.1, D2.2, U2.5
XD_N_RX: C30.2, R9.1, U7.12
XD_N_RXC: C30.1, R5.2
XD_S_A: D5.3, J4.1, R7.1
XD_S_B: D6.3, J4.2, R3.1
XD_S_OUT_A: D5.1, D5.2, U4.7
XD_S_OUT_B: D6.1, D6.2, U4.5
XD_S_RX: C32.2, R11.1, U7.15
XD_S_RXC: C32.1, R7.2
XD_W_A: D7.3, J5.1, R8.1
XD_W_B: D8.3, J5.2, R4.1
XD_W_OUT_A: D7.1, D7.2, U5.7
XD_W_OUT_B: D8.1, D8.2, U5.5
XD_W_RX: C33.2, R12.1, U7.11
XD_W_RXC: C33.1, R8.2
XTAL_IN: C11.1, U1.5, Y1.1
XTAL_OUT: C12.1, U1.6, Y1.2

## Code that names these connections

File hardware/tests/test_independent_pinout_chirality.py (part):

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    # Seeed Studio XIAO ESP32-C6 (102010636, 2x7 module)
    "102010636": {
        "pins": {
            "1": {"VIN_ADC"},       # D0 / GPIO0 ADC1_CH0
            "2": {"NTC_SENSE"},     # D1 / GPIO1 ADC1_CH1
            "3": {"CROWN_BOOT0"},   # D2 / GPIO2
            "4": {"HEAT_PWM"},      # D3 / GPIO21
            "5": {"I2C_SDA"},       # D4 / GPIO22
            "6": {"I2C_SCL"},       # D5 / GPIO23
            "7": {"RS485_TX"},      # D6 / GPIO16 UART1 TX
            "8": {"RS485_RX"},      # D7 / GPIO17 UART1 RX
            "9": {"RS485_DE"},      # D8 / GPIO19 UART1 RTS
            "10": {"CROWN_IRQ"},    # D9 / GPIO20
            "11": {"CROWN_NRST"},   # D10 / GPIO18
            "12": {"+3V3"},         # 3V3 out
            "13": {"GND"},          # GND
            "14": {"+5V_XIAO"},     # 5V in
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    "STM32G431RBT6": {
        "pins": {
            "1": {"+3V3"},           # VBAT
            "5": {"XTAL_IN"},        # PF0-OSC_IN
            "6": {"XTAL_OUT"},       # PF1-OSC_OUT
            "7": {"CROWN_NRST"},     # PG10-NRST
            "13": {"US_AMP_OUT"},    # PA1 OPAMP1_VINP
            "15": {"GND"},           # VSS
            "16": {"+3V3"},          # VDD
            "17": {"US_VREF"},       # PA3 OPAMP1_VINM0 (bias input!)
            "18": {"RAIN_ADC"},      # PA4 ADC2_IN17
            "22": {"I2C_SCL"},       # PC4 I2C2_SCL
            "27": {"GND"},           # VSSA
            "28": {"+3V3A"},         # VREF+
            "29": {"+3V3A"},         # VDDA
            "31": {"GND"},           # VSS
            "32": {"+3V3"},          # VDD
            "33": {"BL_PB12"},       # PB12 SPI2_NSS pull-up
            "38": {"TX_P"},          # PC6 TIM8_CH1
            "39": {"XD_EN_N"},       # PC7
            "40": {"XD_EN_E"},       # PC8
            "41": {"XD_EN_S"},       # PC9
            "42": {"I2C_SDA"},       # PA8 I2C2_SDA
            "44": {"BL_PA10"},       # PA10 USART1_RX pull-up
            "47": {"GND"},           # VSS
            "48": {"+3V3"},          # VDD
            "49": {"SWDIO"},         # PA13
            "50": {"SWCLK"},         # PA14
            "51": {"AS_CS"},         # PA15
            "52": {"TX_N"},          # PC10 TIM8_CH1N
            "53": {"XD_EN_W"},       # PC11
            "54": {"CROWN_IRQ"},     # PC12
            "56": {"AS_SCK"},        # PB3 SPI1_SCK
            "57": {"AS_MISO"},       # PB4 SPI1_MISO
            "58": {"AS_MOSI"},       # PB5 SPI1_MOSI
            "59": {"MUX_S0"},        # PB6
            "60": {"MUX_S1"},        # PB7
            "61": {"CROWN_BOOT0"},   # PB8-BOOT0
            "62": {"AS_IRQ"},        # PB9
            "63": {"GND"},           # VSS
            "64": {"+3V3"},          # VDD
        },
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            "2": {"+3V3"},       # VDD
            "4": {"+3V3"},       # CS high -> I2C mode
            "9": {"GND"},
            "10": {"MAG_CAP"},   # 10 uF SET/RESET reservoir pin
            "11": {"GND"},
            "13": {"+3V3"},      # VDDIO
            "16": {"I2C_SDA"},
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DIODE_POLARITY_RULES: dict[tuple[str, str], dict] = {
    # Main board:
    # D1 SMAJ36A unidirectional 36V TVS: Anode(2)=GND, Cathode(1)=VIN_PROT (reverse biased at +12..32 V)
    ("main", "D1"): {"kind": "2pin", "anode_pad": "2", "cathode_pad": "1", "anode": "GND", "cathode": "VIN_PROT"},
    # D2 SS16 reverse-polarity series Schottky: Anode(2)=VIN_FUSED -> Cathode(1)=VIN_PROT (forward biased)
    ("main", "D2"): {"kind": "2pin", "anode_pad": "2", "cathode_pad": "1", "anode": "VIN_FUSED", "cathode": "VIN_PROT"},
    # D3 SS16 heater flyback Schottky: Anode(2)=HEAT_SW -> Cathode(1)=+12V_HEAT (reverse biased when off/on, clamps flyback)
    ("main", "D3"): {"kind": "2pin", "anode_pad": "2", "cathode_pad": "1", "anode": "HEAT_SW", "cathode": "+12V_HEAT"},
    # D4 PSM712 SOT-23 asymmetric RS-485 surge TVS: 1=RS485_A, 2=RS485_B, 3=GND common anode
    ("main", "D4"): {"kind": "sot23_tvs", "pins": {"1": "RS485_A", "2": "RS485_B", "3": "GND"}},
    # D5 SS14 USB back-feed block Schottky: Anode(2)=+5V -> Cathode(1)=+5V_XIAO
    ("main", "D5"): {"kind": "2pin", "anode_pad": "2", "cathode_pad": "1", "anode": "+5V", "cathode": "+5V_XIAO"},
    # Power board:
    # D1, D2 B360A buck catch Schottkys: Anode(2)=GND -> Cathode(1)=SW (reverse biased when high-side FET conducts)
    ("power", "D1"): {"kind": "2pin", "anode_pad": "2", "cathode_pad": "1", "anode": "GND", "cathode": "LOGIC_SW"},
    ("power", "D2"): {"kind": "2pin", "anode_pad": "2", "cathode_pad": "1", "anode": "GND", "cathode": "HEAT_SW"},
    # Dome board:
    # D1 GUVB-C21SD & D2 GUVA-C22SD zero-bias photodiodes (COB2418: pad 1=Anode on UV_VB, pad 2=Cathode on TIA IN-)
    ("dome", "D1"): {"kind": "2pin", "anode_pad": "1", "cathode_pad": "2", "anode": "UV_VB", "cathode": "UVB_IN"},
    ("dome", "D2"): {"kind": "2pin", "anode_pad": "1", "cathode_pad": "2", "anode": "UV_VB", "cathode": "UVA_IN"},
    # Crown board:
    # D1..D8 BAV99 SOT-23 anti-parallel T/R isolation diodes (pins 1+2 tied on driver OUT, pin 3 on transducer lead)
    ("crown", "D1"): {"kind": "bav99_antiparallel", "drv": "XD_N_OUT_A", "xd": "XD_N_A"},
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    ("crown", "D7"): {"kind": "bav99_antiparallel", "drv": "XD_W_OUT_A", "xd": "XD_W_A"},
    ("crown", "D8"): {"kind": "bav99_antiparallel", "drv": "XD_W_OUT_B", "xd": "XD_W_B"},
    # D9 BAV99 SOT-23 series rail clamp on piezo input: 1(A1)=GND, 2(K2)=+3V3, 3(K1/A2)=PIEZO_IN
    ("crown", "D9"): {"kind": "sot23_clamp", "pins": {"1": "GND", "2": "+3V3", "3": "PIEZO_IN"}},
}


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
    # Verify RS-485 terminal J1 polarity & fail-safe bias: J1.3=RS485_A (pulled to +3V3), J1.4=RS485_B (pulled to GND).
    j1_pads = {p.GetNumber(): p.GetNetname() for p in main_pcb.FindFootprintByReference("J1").Pads() if p.GetNumber()}
    assert j1_pads == {"1": "VIN_RAW", "2": "GND", "3": "RS485_A", "4": "RS485_B"}, f"main J1 wrong pinout: {j1_pads}"
    r_nets = [
        ({p.GetNetname() for p in fp.Pads() if p.GetNumber()}, main_bom[fp.GetReference()]["Value"])
        for fp in main_pcb.Footprints() if ref_prefix(fp.GetReference()) == "R"
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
